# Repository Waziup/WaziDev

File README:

WaziDev
=======

This repository contains everything you need to use [WaziDev](http://www.waziup.io/documentation/wazidev/).

Warning: This repository is work in progress, do not use yet.

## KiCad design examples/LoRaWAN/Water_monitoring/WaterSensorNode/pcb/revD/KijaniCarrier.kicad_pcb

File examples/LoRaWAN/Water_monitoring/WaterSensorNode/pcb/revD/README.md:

# KijaniSpace Carrier — Rev D (laid out, not yet ordered)

> **Start at [`../../README.md`](../../README.md)**. The board as built is
> [`../revC/`](../revC/README.md), and its README documents the generator, the
> checks and the fabrication files; all of that applies here unchanged. This
> folder is a self-contained copy of that generator: `bash gen/build.sh` and
> `bash gen/fab.sh` here only ever write this folder.

## What Rev D changes

The two plug-in modules that are not Atlas parts are now on the board, so the
assembler fits them and only the Atlas circuits and isolators are left to plug in:

| Rev C | Rev D | Why |
| --- | --- | --- |
| RS485 module (MAX13487) on a socket at `U3`, linked to the bus by the terminal `J8` | **THVD1406** transceiver at `U3`, on the board; `J8` is gone | the MAX13487 is specified for 4.75–5.25 V and ran here at 3.3 V; module `TXD`/`RXD` labels differ between batches (one carrier needed its `J4` wires crossed); the module is 53 mm tall |
| Pololu U3V9F12 boost in socket `U1` | **TPS61085** boost (`U8`) on the board; **`U1` stays as a fitted fallback socket**, selected by the solder jumper `JP3` | the module was most of the module cost per board; the socket keeps a known-good way out |
| R7/R8 680 Ω | **470 Ω** | the module's own fail-safe bias is gone, see below |
| — | **SM712** TVS (`D3`) on A/B at the probe terminals | the long cable to the lake |
| transceiver and bias between `3V3REG` and `SWGND` | **between `3V3RS` and `GND`**: `Q6` (AO3401A) switches `3V3RS` from `3V3REG` while `SWGND` is low, `R17` (100 k) holds it off otherwise | in sleep the bus floated up to 3.3 V into the unpowered probes: **0.5 mA per probe**, measured on Rev C (see *Sleep current*) |
| WaziSense beside the carrier | **WaziSense stacked on top**, on three M2.5 standoffs at `H5`–`H7` | both boards take one footprint in the enclosure (see *WaziSense on top*) |

**One firmware change, safe on both carriers:** `parkPinsForSleep()` leaves
D3/D4 as plain inputs instead of with pull-ups (Rev D's unpowered transceiver
would otherwise be fed through `R`). D3/D4, D5, D6 and A1 keep their roles and
timing.

### Pin-out decisions, from the datasheets

- **THVD1406** (SLLSF87A): 1 R, 2 RE, 3 SHDN, 4 D, 5 GND, 6 A, 7 B, 8 VCC.
  `RE` and `SHDN` are tied to VCC: that is the auto-direction mode in TI's own
  application section. In that mode the receiver output is high-impedance
  while the chip drives, so the node hears no echo of its own frame -
  `RS485_ECHOES_OWN_TX` stays 0.
- **TPS61085** (SLVS859B): 1 COMP, 2 FB, 3 EN, 4 PGND, 5 SW, 6 IN, 7 FREQ, 8 SS.
  Rev D copies TI's 3.3 V → 12 V example at 1.2 MHz: `FREQ` and `EN` tied to
  `IN`, 3.3 µH, Schottky to the output, two 10 µF out, 10 µF + 1 µF in,
  47 kΩ / 1.5 nF compensation (TI's table: 47 k / 1.6 nF). One deliberate
  departure: **1 µF soft start instead of 100 nF**, because this output also
  carries `C4` (470 µF, the buffer for the Y511-A's wiper motor), which TI's
  example does not. See *Review* below.
  Feedback 200 k / 22 k: **12.49 V** (1.238 V × (1 + 200/22)), 56 µA through the
  divider. Both probes are inside their range: SEN0680 10–30 V, Y511-A 12–24 V
  - the Pololu's 12 V ±4 % was the one that could dip below 12.

### Why the bias went to 470 Ω

The THVD1406 drives a logic 1 actively for only 4–14 µs after each rising edge
(datasheet, `t_device_auto-dir`); after that the bus is held by the fail-safe
bias. At 4800 baud a bit lasts 208 µs, so the bias carries almost all of every
1. The MAX13487 worked the same way, but its module added its own bias on top
(A–B measured 0.36 V against 0.27 V for the bare network). With 470 Ω the idle
A–B is about **0.37 V**, well above the 0.2 V a receiver needs. The bias sits
on the switched `3V3RS`, so it draws nothing in sleep. TI E2E has reports of
trouble at low baud rates that fit a weak bias; this is the first thing to
check on the first board.

### The fallback, and why both converters can never run at once

```
  +VBATT -- Q1 (switched by D5) -- V12IN -- JP3 centre
                                             +-- pad 1 (joined to the centre by a trace) -- U8 TPS61085 -- D4 --+
                                             +-- pad 3 (open) ---------------------- U1 socket VIN            |
                                                                                     U1 socket VOUT ----------+-- +12V -- C4 -- probes
```

- `V12IN` reaches the on-board converter **or** the Pololu socket's `VIN`,
  never both. Fallback: cut the trace between pads 1 and 2, bridge 2–3, plug
  the Pololu into `U1`.
- A Pololu plugged in with JP3 at 1–2 gets no input and does nothing.
- In fallback, `D4` blocks the Pololu's 12 V from back-feeding the dead
  converter.
- JP3's footprint numbers its pads; the legend on the board explains them.

### Sleep current

**What Rev C does.** Its transceiver and bias sit between `3V3REG` and `SWGND`.
In sleep `D6` lets `SWGND` go, and the bias pulls it - and both bus lines - up
to 3.3 V. The probes are unpowered, but their receiver inputs are referenced
to `GND`, so each line pushes current into each probe. Measured on a Rev C
carrier, 4 Nov 2026, DO probe on the bus, no turbidity probe:

| Sleep, cell side | |
| --- | --- |
| probe cable connected | **0.53 mA** |
| only its A/B wires out of `X3B` | **0.03 mA** (reproducible) |

0.50 mA for one probe, against 2 lines × 3.3 V / 12 kΩ (one unit load) =
0.55 mA predicted. Two probes make about 1.1 mA, the 1.08 mA the hand-wired
node showed: **about 26 mAh a day, more than thirty times the rest of the
node's sleep current.**

**What Rev D does.** The transceiver, `C11` and the bias run from `3V3RS`,
which `Q6` switches from `3V3REG`; its gate is `SWGND`. `D6` on pulls `SWGND`
low and turns `Q6` on (V<sub>GS</sub> −3.3 V); `D6` off lets `R17` pull the gate to the
source and `Q6` turns off. `R8` and the transceiver's ground go to `GND`. In
sleep `3V3RS` drains through `R7`-`RT1`-`R8` and **A and B rest at 0 V**, where
the dead probes are:

| Part | In sleep |
| --- | --- |
| TPS61085, its divider and inductor | behind `Q1`: no supply at all |
| THVD1406, bias, `C11` | `3V3RS` at 0 V; bus at 0 V; THVD1406 logic inputs take up to 5.7 V unpowered (abs. max. independent of VCC) |
| `Q6` | off, V<sub>GS</sub> 0; leakage < 1 µA |
| `R17` | `SWGND` sits at `3V3REG` through it; nothing on `SWGND` (isolators, DS18B20) has a path to `GND` while `D6` is off, so no current |
| SM712 | 0 V |

`R17` costs 33 µA only while `D6` is on. The firmware must not hold D3 high
in sleep (see above): through the dead chip's `R` output that would be up to
0.1 mA.

Keep the isolators fitted. With them bridged, the EZO probes sit on `SWGND`,
and if they share the water with a probe whose housing or reference is on
`GND`, the water itself can pull `SWGND` down and switch `Q6` on in sleep.

## Layout

- **Transceiver** where the module's pin row was, rotated so that `D` and `R`
  face `J4` and `A`/`B` face the bus resistors. `3V3RS` runs under its body
  between the two pad rows, from `Q6` just west of it; `C11` (100 nF) sits
  beside `VCC`. Its ground, `C11`'s and `R8`'s go to vias into the GND pours.
  `R7`'s top takes `3V3RS` down the west side of the body.
- **`Q6`/`R17`** between the `+VBATT` run at x 61 and `RS_TX`. The gate's
  `SWGND` drops from the y 22 trunk on the back at x 60.25 (clear of `J3`'s
  and `J4`'s pads). `3V3REG` reaches `R11`/`R12` on the back at y 42.4,
  between the `D5` lane (y 43) and the `SWGND` via at (73.5, 41.5), because
  the run under the transceiver is `3V3RS` now.
- The `SWGND` trunk crosses the `D5` lane (back layer, y 43) by hopping over
  on the front between two vias, then turns for the isolators. The `SWGND`
  pour of Rev C is gone: nothing that needed it is left on `SWGND`.
- **Boost** in the empty area above the probe terminals, right beside the
  `+12V` run it feeds. The switching loop - `SW`, `L1`, `D4`, `C14`/`C15`,
  `PGND` - is one tight ring on the front layer below the IC; soft start,
  compensation and divider sit above it. Its input comes from `JP3` by the
  Pololu socket: down to the back at x 43 and across at y 84, the only place
  where the back layer is clear of the `+VBATT`, `+12V` and `ISO_VIN` lanes.
- `JP3` sits just east of the Pololu module's outline, not under it.

## WaziSense on top

The WaziSense v2 sits above the carrier on three **20 mm M2.5 standoffs**,
component side up and turned 180°, its origin at KiCad (66.5, 45.25). Its
outline covers x 48.2–118.6, y 31.0–83.9: the isolators, `C4`/`C8`, the
transceiver and the legend lie under it; the J-row, the probe terminals, the
EZO sockets, `X1` and the boost block stay outside. Its edge stops about 4 mm
short of the screws of the carrier's J-row.

| Hole | KiCad (mm) | What had to move |
| --- | --- | --- |
| `H5` | (113.49, 54.39) | nothing; the last legend lines are shorter now |
| `H6` | (58.12, 45.00) | `+VBATT` from `Q5` drops at x 54.3 instead of 56; the feed to `J6` leaves it at y 37 instead of the y 48 rail; `D5` (back) loops south of the hole at y 48.8 |
| `H7` | (61.67, 81.45) | `BOOST_IN` surfaces at (56.5, 84) and goes north round the hole at y 77.4 into `C12`; the boost block's row of labels closed up west of it, same order |

- **M2.5, 2.7 mm holes.** The WaziSense's own holes are 3.0 mm (read off its
  Gerbers), too tight for M3.
- **Bare board round each hole.** No track or via of any net within 3.2 mm of
  a centre, on either layer: the standoff's hex foot (5 mm across flats,
  2.9 mm to a corner) on the front, the screw head on the back. `check.py`
  checks it (section 6) and also fails if there are not exactly three.
- **Height.** The tallest parts under the WaziSense are `C4`/`C8` (470 µF,
  10 × 13 mm) and the isolators in their sockets. 20 mm standoffs leave about
  5 mm over the capacitors once the WaziSense's own pin ends (about 2 mm) are
  counted. Measure an isolator in its socket before buying the standoffs.
- **The J-row keeps its order.** Turning the WaziSense mirrors its terminal
  order against the carrier's, so the wires between the blocks cross. A
  reorder was tried and dropped: `J2` (SW_1) would land on `H4`, and `SWGND`,
  `3V3P`, `A1` and `OW_DATA` would have to cross the whole board to the
  circuits on the west side they serve. **Wire the carrier's terminals first,
  then mount the WaziSense.** Within each block the pins keep their order, so
  every wire of a block has the same length:

| Carrier | WaziSense | Across | Straight line with the 20 mm rise |
| --- | --- | --- | --- |
| `J2` | SW_1 | 77.5 mm | 80 mm |
| `J3` | ANALOG | 48.9 mm | 53 mm |
| `J4` | DIGITAL | 23.7 mm | 31 mm |
| `J5A`/`J5B` | I2C | 15.3 mm | 25 mm |
| `J6` | BAT_IN, on the WaziSense's far edge | 52–54 mm | 56–58 mm |

Cut each wire with enough slack to lift the WaziSense off for service.

## A generator bug Rev D fixed

`mkpcb.py` wrote every pad with its library angle. A board file stores pad
angles **absolute**, so a rotated footprint kept its pads in library
orientation. On round and square pads that is invisible; on Rev C it affected
only `R13` (0603, rotated 270°), whose near-square pads came out turned 90° -
harmless. On Rev D's SOIC it would have made neighbouring pads overlap. The pad
angle now gets the footprint rotation added. The same bug was the cause of the
14 `lib_footprint_mismatch` warnings in Rev C's DRC; Rev D has none.

`check.py` and `pads.py` now use each pad's real rectangle (rotation included)
instead of a circle of its long half-side, and accept T-junctions. The circle
called neighbouring SOIC pads 0.6 mm apart a collision.

## State

| Check | Result |
| --- | --- |
| `check.py` (endpoints, pad/track/via clearance, barriers, bare board round the three WaziSense standoffs) | clean |
| `pour.py` | every GND pad reachable through the pour |
| KiCad DRC, errors | **0 violations, 0 unconnected** |
| KiCad DRC, warnings | the same 21 silkscreen touches between ganged terminal pairs as Rev C (intended); nothing else |
| `silkcheck.py`, `cplcheck.py`, `vendorcheck.py`, `bomsync.py`, `fabcheck.py`, `zipcheck.py` | pass |
| `netcheck.py` (new: firmware pins, both chips pin by pin, SWGND, the switched bus supply, JP3, probe supply) | 94 requirements hold |
| `out/FACTS.md` | 75 footprints (72 before the WaziSense standoff holes `H5`–`H7`), 68 placed parts, 30 BOM lines, 7 Extended SMT types |

Parts read off JLCPCB's listing on 4 Nov 2026, all marked "Economic and
Standard": THVD1406DR `C5215918` (5,827 in stock), TPS61085DGKR `C113659`
(26,333), SWPA4030S3R3MT `C15269` (21,889, Isat 3.6 A), SM712 `C293966`
(121,381), 1.5 nF `C1595`; Basic: SS14 `C2480`, 10 µF 50 V 1206 `C13585`,
47 k `C25819`, 200 k `C25811`, 22 k `C31850`, 470 Ω `C23179`. `Q6` and `R17`
join existing BOM lines (AO3401A `C15127`, 100 k `C25803`): no new line, no
new feeder.

**Cost.** Extended feeders 7 × 3 USD and 78 through-hole joints: about 26 USD
once per order (Rev C: 11 USD). Each board saves the Pololu and the RS485 module,
about 12 € net of the new parts, so Rev D is cheaper from the second assembled
board on.

## Review before ordering (4 Nov 2026)

### Placement rotations, read off the vendor footprints

JLCPCB places by the EasyEDA footprint on each part page. Calibrated on the
AO3401A, whose footprint there is KiCad's SOT-23 turned 180° - the correction
the Rev C placement view had shown:

| Part | JLCPCB footprint against KiCad's | `JLC_ROT_FP` | CPL |
| --- | --- | --- | --- |
| `U3` THVD1406, SOIC-8 | pin 1 bottom left, pins in rows: turned 90° | 270 | 180 |
| `U8` TPS61085, MSOP-8 | the same | 270 | 270 |
| `D3` SM712, SOT-23 | the AO3401A's layout, pin 3 common | 180 (existing) | 90 |
| `D4` SS14, SMA | cathode left, as KiCad | 0 | 0 |
| `L1` SWPA4030 | pads left and right, as KiCad | 0 | 0 |

Still check pin 1 of `U3`/`U8` and `D4`'s band in the placement view.

### Operating states

| State | What Rev D does there | Verdict |
| --- | --- | --- |
| Sleep | `Q6` off, `3V3RS` and the bus at 0 V with the probes; `U8` has no supply (`Q1` off); the firmware parks D3/D4 as plain inputs | Rev C's 0.5 mA per probe gone; expect Rev C's 0.03 mA base |
| 3.3 V rail on (D6) | `Q6` on; THVD1406 1.7 mA + bias 3.1 mA (Rev C: 2.2 mA bias) + `R17` 33 µA | +0.9 mA, sensor phase only |
| 12 V switch-on (D5) | as with the Pololu, which has the same inductor-and-diode path: the cell charges `C4` through `L1`/`D4` the moment `Q1` closes, 8-10 A for 0.1-0.3 ms (model) - Rev C does the same on every cycle without resets. Then the soft start: with 100 nF the current limit reached 2.4 A within 5 ms and held it until `C4` was charged, +VBATT down to 2.5 V with a weak cell at 3.3 V; with **1 µF** about 1.1 A over ~27 ms, +VBATT 2.86 V worst / 3.05 V healthy cell | **`C16` 100 nF → 1 µF** (Basic part already on the BOM) |
| Measuring: 12 V and isolators on | during the wiper sweep the Y511-A draws 1.5–2 W, up to 0.6 A from the cell (measured on the earlier builds). That is ~0.16 A out of `U8` at 12.49 V, against ~0.37 A it can deliver at 3.3 V in (2.0 A minimum switch limit, 3.3 µH, 1.2 MHz). Inductor peak ~1.2 A (`L1` Isat 3.6 A), `D4` 0.16 A average (1 A part), `F1` 2.6 A hold. The wiper's start is buffered by `C4`. 12.49 V against the Y511-A's 12 V minimum (Rev C: 12 V ±4 %, sweeps cleanly) | ok, 2× margin |
| RS485 traffic | driver on within 10 µs of D falling (≤ 10 % of a 9600-baud start bit), drives a 1 for 4-14 µs, then the 0.37 V bias holds it; receiver off while driving, so no echo | ok; first-board gate |
| LoRa TX/RX | the rails are off before the radio sends | ok |
| Cell at 3.0 V | TPS61085 runs to 2.3 V; 0.3-0.4 A output capability at 3.0 V in. Rev C measured, 4 Nov 2026 (bench supply, DO probe only): a full cycle at 3.05 V, bootloop at 3.0 V. The firmware stops measuring below 3.50 V and since that day also checks the cell at start-up, so a restart at an empty cell no longer switches the 12 V rail on | ok, 0.45 V above the floor |
| Full cell / charging | 4.2 V against IN 6 V max | ok |
| USB only, no cell | the battery domain sits at ~2.8 V: the Pololu stopped regulating there, the TPS61085 does not and pulls up to ~1 A from a back-fed domain | bench rule stands: cell connected |
| Fallback, JP3 at 2-3 | `D4` blocks back-feed; `U8` unpowered; FB sees `+12V` through 200 kΩ, tens of µA, IN stays under its 2.3 V start | ok |
| Pololu plugged, JP3 at 1-2 | its VIN is open | does nothing |
| A/B shorted to +12V at a terminal | THVD1406 ±16 V bus fault rating, `D3` | better than Rev C |
| Temperature | THVD1406 −40…125 °C, TPS61085 characterised −40…85 °C, X5R to 85 °C | ok in the enclosure |
| Noise | the boost runs during the pH/EC reads (firmware order), ≥ 20 mm from the pH input, in another ground domain; Rev C's Pololu ran then too | compare on the first board |

### The sleep-current question, answered

The review predicted that the floating bus leaks into the unpowered probes,
about 0.55 mA per probe. Rev C measured 0.50 mA for one probe (*Sleep current*
above), so Rev D's copper changed the same day: `Q6`, `R17`, `3V3RS`, the
transceiver block on `GND`, the `SWGND` pour removed, and the firmware's D3/D4
parking. `netcheck.py` now also holds the rule itself: only `Q6` feeds
`3V3RS`, only the transceiver block is on it, and nothing else touches A or B.

### Before ordering

1. JLCPCB placement view: pin 1 of `U3` and `U8`, cathode band of `D4`, and
   `Q6` with its single pin (drain) towards `U3` (SOT-23 rule, CPL 90).
2. The 1:1 print (`out/KijaniCarrier-top-1zu1.pdf`) with the Pololu and a
   SOIC-8 / SMA part on it.
3. On the same print: lay the WaziSense on it, turned 180°, with its terminal
   row towards the J-row. Its three holes must sit over `H5`–`H7`; they were
   drawn from its Gerbers, not measured on a board.

## On the first board

1. **12 V rail:** 12.4–12.6 V without load and with both probes; ripple on a
   scope if one is at hand; a load step (the Y511-A's wiper) without
   oscillation. `C4`'s 470 µF hangs on the output too, which TI's example does
   not have.
2. **RS485:** `RS485Drive` (idle A–B about 0.37 V, collapsing while driving),
   then both probes at 4800 and 9600 baud with the main firmware.
3. **Sleep current**, everything connected, both probes on the bus: expect
   Rev C's 0.03 mA base, not its 0.53 mA. With the FTDI unplugged. While the
   node boots and sends, short the meter with a clip lead; take the lead off
   only once it sleeps, or the meter's shunt can brown the node out (most
   likely why the Rev C measurement began with five resets in a row). Then `SWGND` with D6 off: about 3.3 V
   (`R17`), and `3V3RS`: 0 V.
4. **Fallback once:** cut JP3 1–2, bridge 2–3, plug the Pololu in - 12 V must
   come back, then restore.

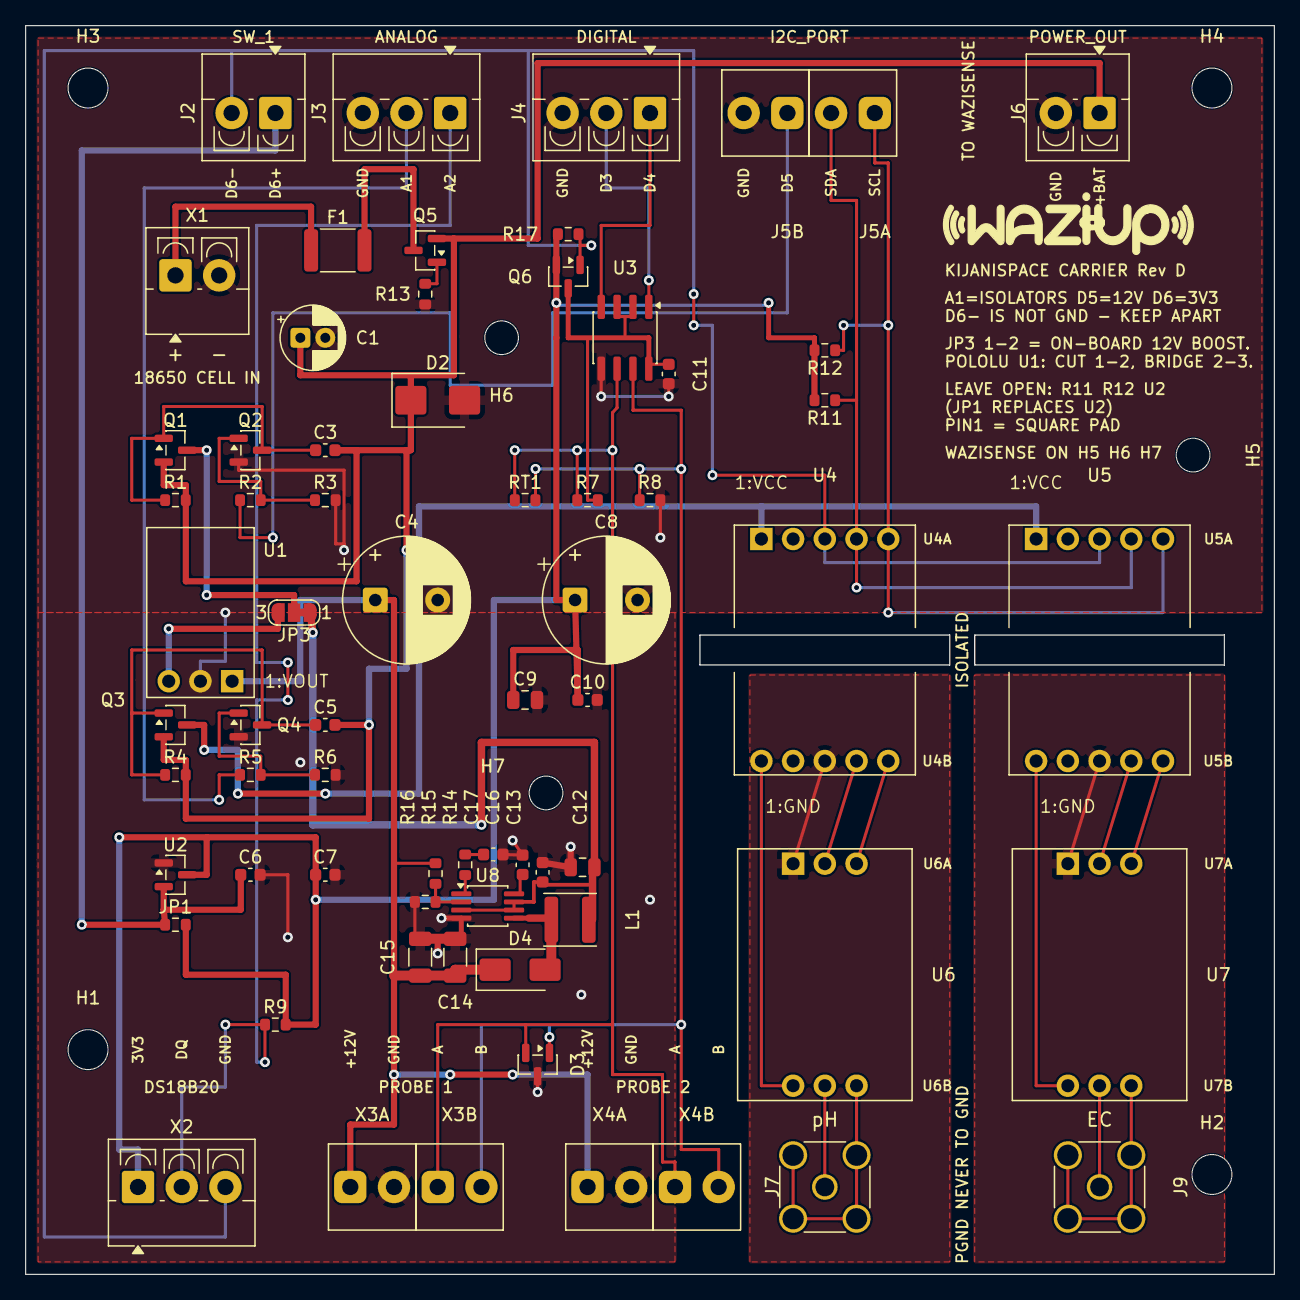
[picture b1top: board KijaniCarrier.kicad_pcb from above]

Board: 2 copper layers, 100.0 x 100.0 mm, 75 parts (0 on the bottom side), 44 nets.

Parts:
C1: 100uF; CP_Radial_D5.0mm_P2.00mm
C3, C5, C10, C11: 100nF; C_0603_1608Metric
C4, C8: 470uF; CP_Radial_D10.0mm_P5.00mm
C6, C7, C13, C16: 1uF; C_0603_1608Metric
C9, C12: 10uF; C_0805_2012Metric
C14, C15: 10uF 50V; C_1206_3216Metric
C17: 1.5nF; C_0603_1608Metric
D2: SMBJ5.0A; D_SMB
D3: SM712; SOT-23
D4: SS14; D_SMA
F1: PTC 2.6A; R_1812_4532Metric
H1, H2, H3, H4: M3; MountingHole_3.2mm_M3
H5, H6, H7: M2.5 WaziSense; MountingHole_2.7mm_M2.5
J2: SW_1; TerminalBlock_4Ucon_1x02_P3.50mm_Vertical
J3: ANALOG; TerminalBlock_4Ucon_1x03_P3.50mm_Vertical
J4: DIGITAL; TerminalBlock_4Ucon_1x03_P3.50mm_Vertical
J5A, J5B: I2C_PORT; TerminalBlock_KF350_1x02
J6: BAT_IN; TerminalBlock_4Ucon_1x02_P3.50mm_Vertical
J7: SMA pH; SMA_Amphenol_132291_Vertical
J9: SMA EC; SMA_Amphenol_132291_Vertical
JP1: 0R DNP; R_0603_1608Metric
JP3: BOOST SEL; SolderJumper-3_P1.3mm_Bridged12_RoundedPad1.0x1.5mm_NumberL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
L1: 3.3uH; L_Sunlord_SWPA4030S
Q1, Q3, Q5, Q6: AO3401A; SOT-23
Q2, Q4: 2N7002; SOT-23
R1, R3, R4, R6, R13, R17: 100k; R_0603_1608Metric
R2, R5: 10k; R_0603_1608Metric
R7, R8: 470R; R_0603_1608Metric
R9: 4k7; R_0603_1608Metric
R11, R12: 47k DNP; R_0603_1608Metric
R14: 47k; R_0603_1608Metric
R15: 200k; R_0603_1608Metric
R16: 22k; R_0603_1608Metric
RT1: 120R; R_0603_1608Metric
U1: U3V9F12; Pololu_U3V9F12
U2: MCP1700-3302; SOT-23
U3: THVD1406; SOIC-8_3.9x4.9mm_P1.27mm
U4: BE-IVI pH; BE_IVI_Isolator
U5: BE-IVI EC; BE_IVI_Isolator
U6: EZO-pH; EZO_Circuit
U7: EZO-EC; EZO_Circuit
U8: TPS61085; MSOP-8_3x3mm_P0.65mm
X1: CELL; TerminalBlock_4Ucon_1x02_P3.50mm_Vertical
X2: DS18B20; TerminalBlock_4Ucon_1x03_P3.50mm_Vertical
X3A, X3B: PROBE1; TerminalBlock_KF350_1x02
X4A, X4B: PROBE2; TerminalBlock_KF350_1x02

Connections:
3V3P: C6.1, J2.1, JP1.1, U2.2
3V3REG: C7.1, C8.1, C9.1, C10.1, JP1.2, Q6.2, R9.2, R11.2, R12.2, R17.1, U2.3, X2.1
3V3RS: C11.1, Q6.3, R7.2, U3.2, U3.3, U3.8
+12V: C4.1, C14.1, C15.1, D4.1, R15.2, U1.1, X3A.1, X4A.1
+VBATT: C1.1, C3.2, C5.2, D2.1, J6.1, Q1.2, Q3.2, Q5.2, R1.2, R4.2
A1: J3.2, R5.1
BOOST_COMP: R14.1, U8.1
BOOST_FB: R15.1, R16.2, U8.2
BOOST_IN: C12.2, C13.1, JP3.1, L1.2, U8.3, U8.6, U8.7
BOOST_RC: C17.1, R14.2
BOOST_SS: C16.1, U8.8
BOOST_SW: D4.2, L1.1, U8.5
D5: J5B.1, R2.1
EC_PGND: J9.2, U7.6
EC_PRB: J9.1, U7.5
GND: C1.2, C4.2, C6.2, C7.2, C8.2, C9.2, C10.2, C11.2, C12.1, C13.2, C14.2, C15.2, C16.2, C17.2, D2.2, D3.3, J3.3, J4.3, J5B.2, J6.2, Q2.2, Q4.2, R3.2, R6.2, R8.2, R13.2, R16.1, U1.2, U2.1, U3.5, U8.4, X1.2, X3A.2, X4A.2
ISO1_3V9: U4.6, U6.4
ISO1_A: U4.9, U6.2
ISO1_B: U4.10, U6.3
ISO1_GND: U4.8, U6.1
ISO2_3V9: U5.6, U7.4
ISO2_A: U5.9, U7.2
ISO2_B: U5.10, U7.3
ISO2_GND: U5.8, U7.1
ISO_VIN: Q3.3, U4.1, U5.1
OW_DATA: J3.1, R9.1, X2.2
PH_PGND: J7.2, U6.6
PH_PRB: J7.1, U6.5
POLOLU_VIN: JP3.3, U1.3
Q1_G: C3.1, Q1.1, Q2.3, R1.1
Q2_G: Q2.1, R2.2, R3.1
Q3_G: C5.1, Q3.1, Q4.3, R4.1
Q4_G: Q4.1, R5.2, R6.1
Q5_G: Q5.1, R13.1
RS485_A: D3.2, R7.1, RT1.1, U3.6, X3B.1, X4B.1
RS485_B: D3.1, R8.1, RT1.2, U3.7, X3B.2, X4B.2
RS_RX: J4.2, U3.1
RS_TX: J4.1, U3.4
SCL: J5A.1, R12.1, U4.5, U5.5
SDA: J5A.2, R11.1, U4.4, U5.4
SWGND: J2.2, Q6.1, R17.2, U4.3, U5.3, X2.3
V12IN: JP3.2, Q1.3
VB1: F1.1, X1.1
VB2: F1.2, Q5.3

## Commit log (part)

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2019-12-09 Makefile
2019-12-10 minimal
2019-12-10 getSensorValue
2019-12-12 Add DHT11
2019-12-12 clean
2019-12-12 DHT library
2019-12-12 typo
2019-12-12 DS18B20
2019-12-12 DHT11 with LoRa
2019-12-13 Makefiles
2019-12-14 clean all
2019-12-19 convert example
2020-01-08 demo temp
2020-01-08 ping ack
2020-01-08 moves
2020-01-17 LoRaWAN
2020-01-23 LoRaWAN fixes
2020-02-11 subs
2020-02-11 Rename Utils
2020-02-17 Simplify
2020-02-17 LoraWAN LPP
2020-02-21 Utils
2020-04-03 WaziDev tests
2020-04-03 remove submodule
2020-04-03 Squashed 'libraries/WaziDev/' content from commit fb9d311
    git-subtree-dir: libraries/WaziDev
    git-subtree-split: fb9d311a7302fbeb7b7b79e964891af3fbfb4f01
2020-04-03 WaziDev
2020-04-03 I2CIO
2020-04-03 SX1272
2020-04-03 README
2020-06-26 update Makefiles
2020-06-26 LoraWAN LPP LMIC
2020-07-28 remove old example
2020-07-28 add new example
2020-08-03 LMIC
2020-08-03 SF12
2020-08-20 change single channel LMIC
2020-11-09 small changes
2020-11-16 display received data
2020-11-16 length bug
2020-12-09 actuation
2021-01-12 Add Fritzing files
2021-01-13 Cleanup
2021-01-13 Add libraries
2021-01-13 Update libraries
2021-01-13 Move examples
2021-01-13 Update WaziDev
2021-01-15 Remove submodules
2021-01-15 Embed libraries
2021-01-15 Add examples
2021-01-15 Bump
2021-01-21 Improve & Refactor
2021-01-26 Improve Docs
2021-01-26 Fix wiring
2021-01-27 putting back sensors/actuators examples
2021-02-03 update main.cpp with a small two line correction
    correct case LPP_DIGITAL_INPUT and case LPP_DIGITAL_OUTPUT in lines 156 and 163
2021-02-04 splitting the keys for more flexibility
2021-02-04 Adding global variable matching the library AES-128
2021-02-04 Squashed 'libraries/WaziDev/' changes from fb9d311..2ab80a7
    2ab80a7 WaziDev
    git-subtree-dir: libraries/WaziDev
    git-subtree-split: 2ab80a7b261d2622284983987dbfcb51ca839446
2021-02-04 Squashed 'libraries/WaziDev/' changes from 2ab80a7..626a927
    626a927 Merge commit 'b79f950faa8392ffcda3c93a424adfd89edeb4c5'
    821ae40 Adding global variable matching the library AES-128
    01b337e Merge wazidev-lib
    bb793ac Bump
    92da3af Embed libraries
    9b535c4 Remove submodules
2021-02-05 .env file
2021-02-24 Update DHT_RGB-LED
2021-02-24 Bump XLPP
2021-03-10 Actuation with JSON
2021-04-08 Tested Code for DHT 11 with Wazidev
    Data to Waziup.
2021-04-19 test script
2021-05-03 Jenkinsfile
2021-05-03 tests
2021-05-03 test
2021-05-03 docker
2021-06-15 Wazisense Example added
2021-06-28 solar panel read added
2021-06-28 docs updated
2021-06-29 Soil moisture sensor added
2021-06-30 wazidev hardware test added
2021-06-30 readme added
2021-06-30 note added
2021-09-01 bug example
2021-09-16 key bug
2021-09-29 Changes to Jenkinsfile to include libraries for automatic build. Added desciption for better usability .
2021-09-29 Renamed NEO-6M, added comments, updated jenkinsfile.
2021-12-20 Add flag to turn off debugging
2021-12-20 LoRaWAN test
2022-02-01 remove Makefiles
2022-02-02 python API
2022-02-04 JEnkins
2022-07-14 service
2023-01-14 AM3215 sensor with LoRaWAN and Battery Monitoring
    Tested and Working
2024-06-14 Irrigation folder with flow meter and actuation for pump
2024-06-17 fixed LoRa
2024-06-21 actuation of pump with flow meter, tested and calibrated
2024-07-24 irrigation script v1
2024-09-09 added voltage messurement and refined irrigation script to actuate a pump
2024-12-12 added script for capacitive soil moisture sensor
2025-01-23 Add actuator
2025-01-28 Expose more WaziDev features
    Clear logging
    Add setLoRaPower
    Add setLoRaSyncWord
2025-01-28 Add LoRaWAN class A example
2025-01-28 Add LoRaWAN class C example
2025-01-28 Rename WaziDev Chat example
2025-01-28 Streamline WaziDev Chat
2025-05-01 test LoRa
2025-05-02 change DevAddr
2025-05-02 test ino
2025-05-14 Updated Actuation code for ChirpStack V4
2025-07-10 added some scripts for actuation: general and flow meter
2025-08-15 refinements irrigation actuator
